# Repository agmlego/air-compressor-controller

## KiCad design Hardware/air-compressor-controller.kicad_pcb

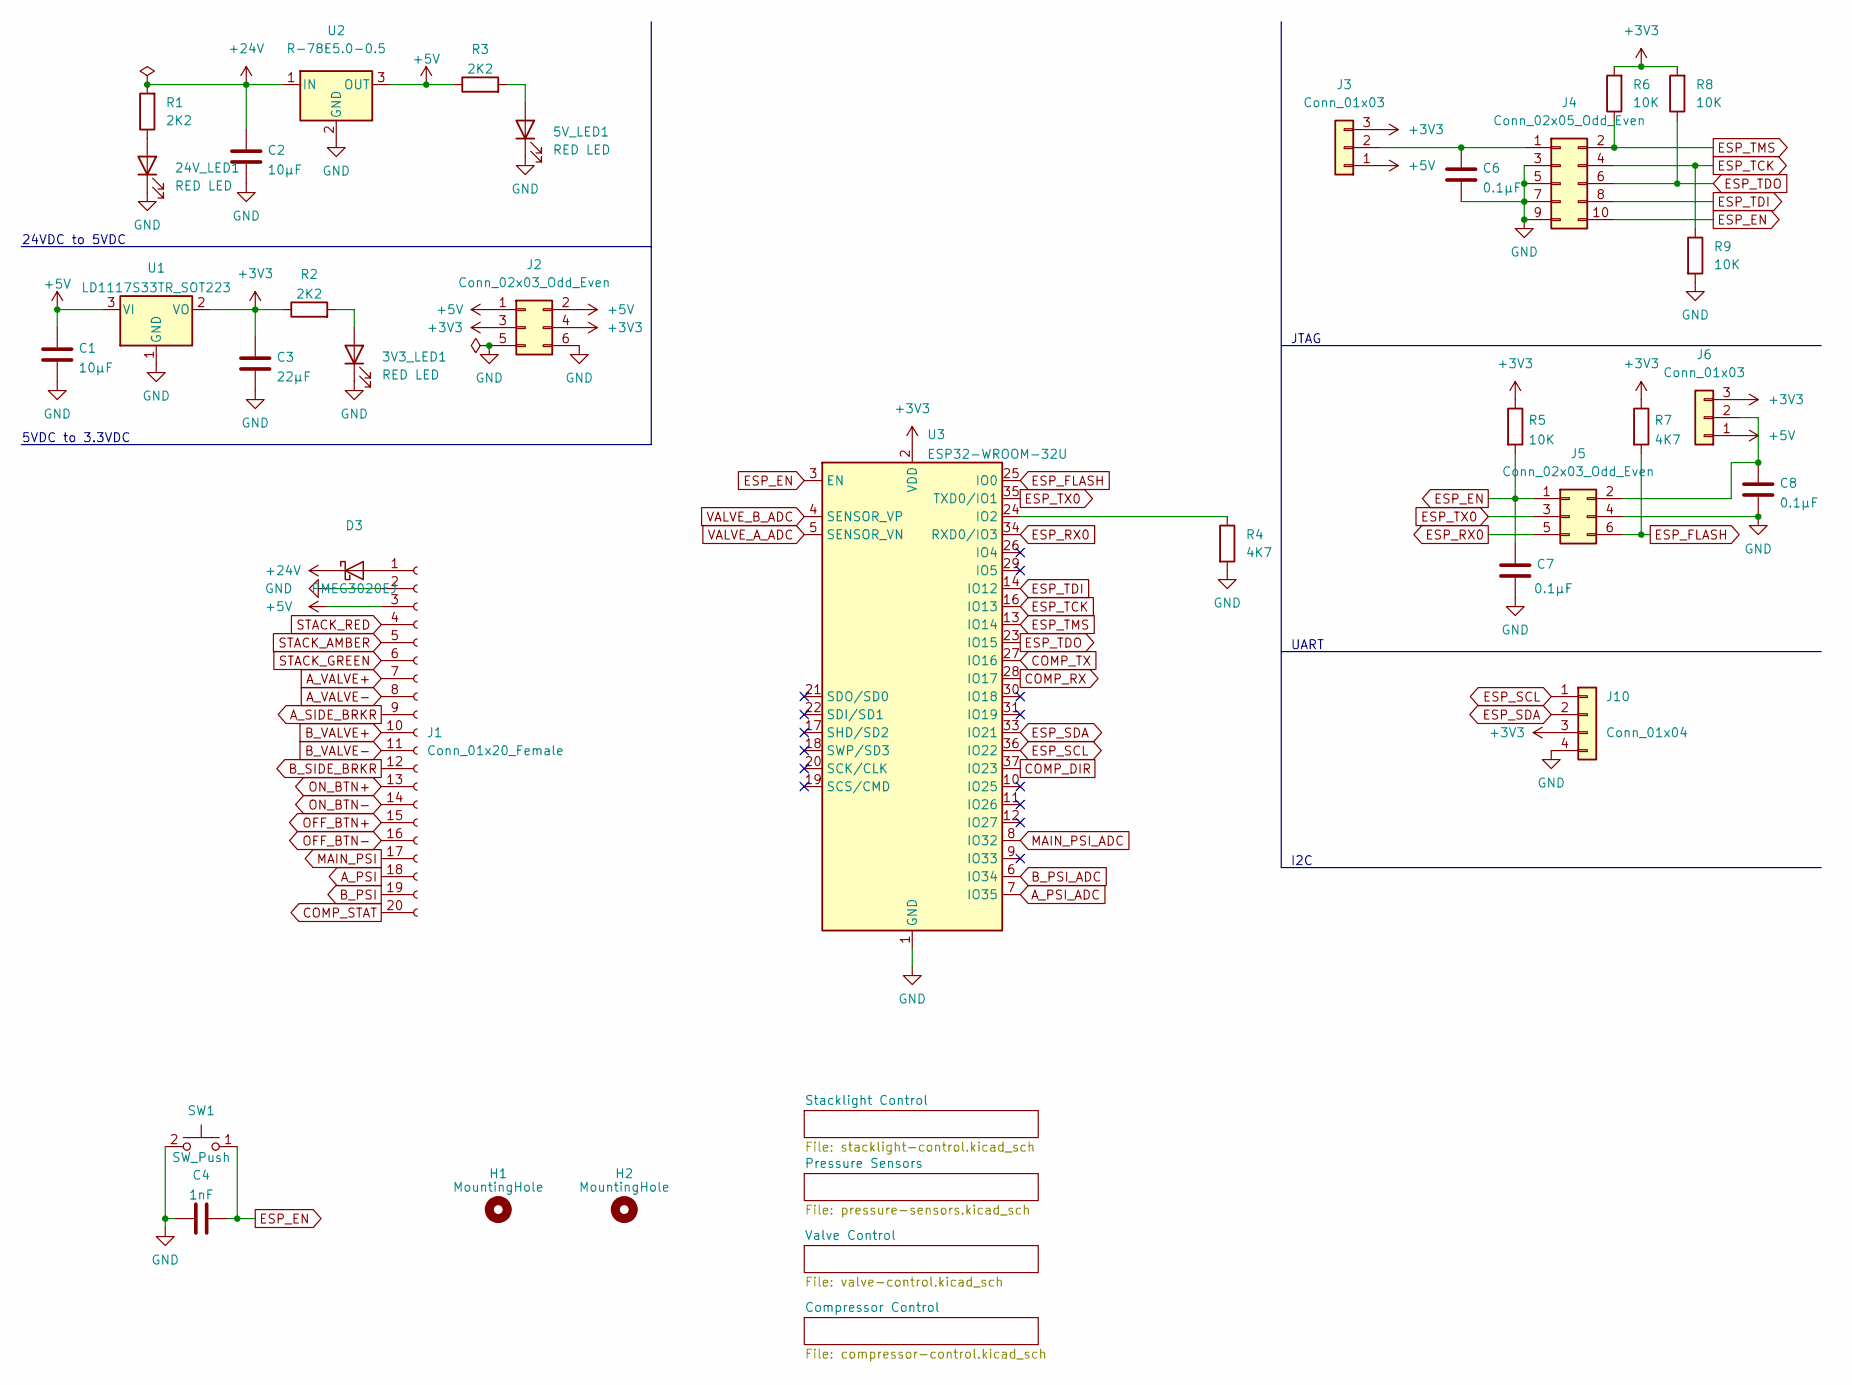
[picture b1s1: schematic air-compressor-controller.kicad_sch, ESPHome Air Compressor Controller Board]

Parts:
3V3_LED1, 5V_LED1, 24V_LED1: RED LED; LED_0603_1608Metric
C1, C2: 10µF; CP_Elec_4x4.5
C3: 22µF; CP_Elec_4x4.5
C4: 1nF; C_0603_1608Metric
C6, C7, C8: 0.1µF; C_0603_1608Metric
D3: PMEG3020EJ; D_SOD-323F
H1, H2: MountingHole; MountingHole_3.2mm_M3_Pad
J1: Conn_01x20_Female; Wago_734-180_1x20_P3.50mm_Horizontal
J2: Conn_02x03_Odd_Even; PinHeader_2x03_P2.54mm_Vertical_SMD
J3, J6: Conn_01x03; PinHeader_1x03_P2.54mm_Vertical_SMD_Pin1Left
J4: Conn_02x05_Odd_Even; Tag-Connect_TC2050-IDC-NL_2x05_P1.27mm_Vertical
J5: Conn_02x03_Odd_Even; Tag-Connect_TC2030-IDC-NL_2x03_P1.27mm_Vertical
J10: Conn_01x04; PinHeader_1x04_P2.54mm_Vertical_SMD_Pin1Left
R1, R2, R3: 2K2; R_0603_1608Metric
R4, R7: 4K7; R_0603_1608Metric
R5, R6, R8, R9: 10K; R_0603_1608Metric
SW1: SW_Push; SW_Tactile_SPST_Angled_PTS645Vx39-2LFS
U1: LD1117S33TR_SOT223; SOT-223-3_TabPin2
U2: R-78E5.0-0.5; Converter_DCDC_RECOM_R-78E-0.5_THT
U3: ESP32-WROOM-32U

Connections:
+3V3: C3.1, J2.3, J2.4, J3.3, J6.3, J10.3, R2.1, R5.1, R6.2, R7.1, R8.2, U1.2 (VO), U3.2 (VDD); also elsewhere on the board
+5V: C1.1, J1.3, J2.1, J2.2, J3.1, J6.1, R3.1, U1.3 (VI), U2.3 (OUT); also elsewhere on the board
+24V: C2.1, D3.1 (K), R1.2, U2.1 (IN); also elsewhere on the board
A_PSI: J1.18; also elsewhere on the board
A_PSI_ADC: U3.7 (IO35); also elsewhere on the board
A_SIDE_BRKR: J1.9; also elsewhere on the board
A_VALVE+: J1.7; also elsewhere on the board
A_VALVE-: J1.8; also elsewhere on the board
B_PSI: J1.19; also elsewhere on the board
B_PSI_ADC: U3.6 (IO34); also elsewhere on the board
B_SIDE_BRKR: J1.12; also elsewhere on the board
B_VALVE+: J1.10; also elsewhere on the board
B_VALVE-: J1.11; also elsewhere on the board
COMP_DIR: U3.37 (IO23); also elsewhere on the board
COMP_RX: U3.28 (IO17); also elsewhere on the board
COMP_STAT: J1.20; also elsewhere on the board
COMP_TX: U3.27 (IO16); also elsewhere on the board
ESP_EN: C4.2, C7.1, J4.10, J5.1, R5.2, SW1.1, U3.3 (EN); also elsewhere on the board
ESP_FLASH: J5.6, R7.2, U3.25 (IO0)
ESP_RX0: J5.5, U3.34 (RXD0/IO3)
ESP_SCL: J10.1, U3.36 (IO22); also elsewhere on the board
ESP_SDA: J10.2, U3.33 (IO21); also elsewhere on the board
ESP_TCK: J4.4, R9.1, U3.16 (IO13)
ESP_TDI: J4.8, U3.14 (IO12)
ESP_TDO: J4.6, R8.1, U3.23 (IO15)
ESP_TMS: J4.2, R6.1, U3.13 (IO14)
ESP_TX0: J5.3, U3.35 (TXD0/IO1)
GND: 3V3_LED1.1 (K), 5V_LED1.1 (K), 24V_LED1.1 (K), C1.2, C2.2, C3.2, C4.1, C6.2, C7.2, C8.2, J1.2, J2.5, J2.6, J4.3, J4.5, J4.7, J4.9, J5.4, J10.4, R4.2, R9.2, SW1.2, U1.1 (GND), U2.2 (GND), U3.1 (GND), U3.15 (GND), U3.38 (GND), U3.39 (GND); also elsewhere on the board
MAIN_PSI: J1.17; also elsewhere on the board
MAIN_PSI_ADC: U3.8 (IO32); also elsewhere on the board
unnamed: 3V3_LED1.2 (A), R2.2
unnamed: 5V_LED1.2 (A), R3.2
unnamed: 24V_LED1.2 (A), R1.1
unnamed: C6.1, J3.2, J4.1
unnamed: C8.1, J5.2, J6.2
unnamed: D3.2 (A), J1.1
unnamed: R4.1, U3.24 (IO2)
OFF_BTN+: J1.15; also elsewhere on the board
OFF_BTN-: J1.16; also elsewhere on the board
ON_BTN+: J1.13; also elsewhere on the board
ON_BTN-: J1.14; also elsewhere on the board
STACK_AMBER: J1.5; also elsewhere on the board
STACK_GREEN: J1.6; also elsewhere on the board
STACK_RED: J1.4; also elsewhere on the board
VALVE_A_ADC: U3.5 (SENSOR_VN); also elsewhere on the board
VALVE_B_ADC: U3.4 (SENSOR_VP); also elsewhere on the board

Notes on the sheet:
JTAG
UART
I2C
24VDC to 5VDC
5VDC to 3.3VDC

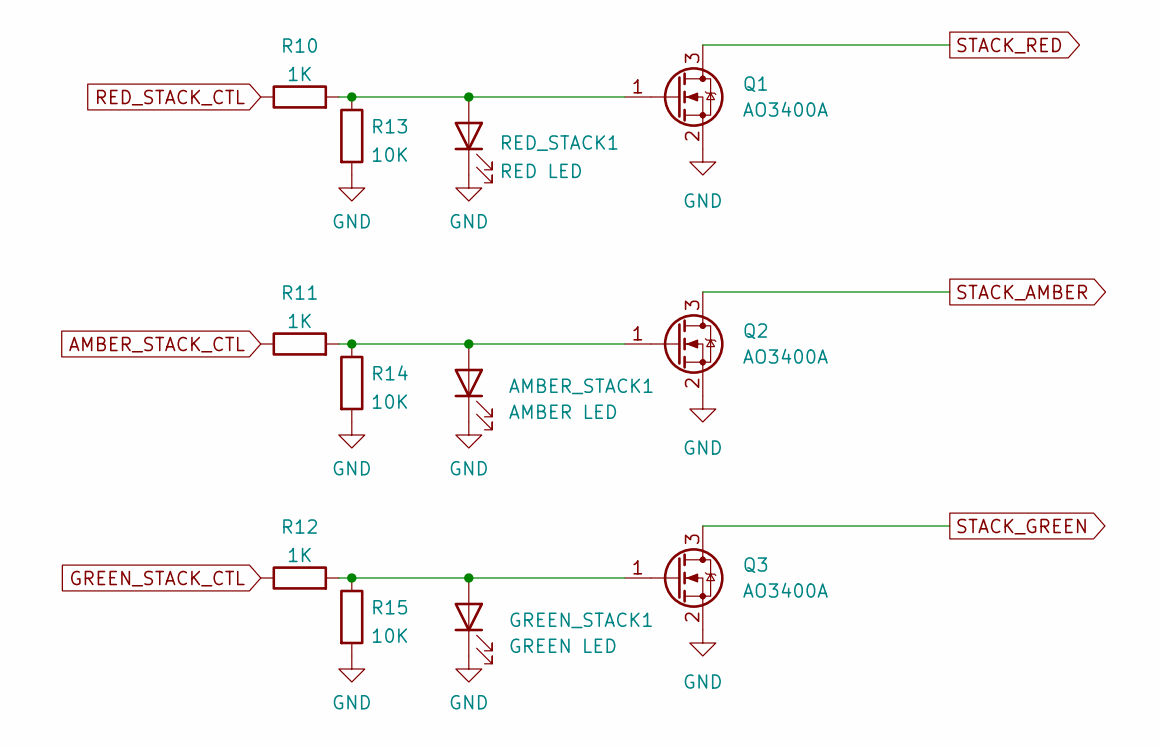
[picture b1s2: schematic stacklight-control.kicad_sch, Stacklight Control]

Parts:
AMBER_STACK1: AMBER LED; LED_0603_1608Metric
GREEN_STACK1: GREEN LED; LED_0603_1608Metric
Q1, Q2, Q3: AO3400A; SOT-23
R10, R11, R12: 1K; R_0603_1608Metric
R13, R14, R15: 10K; R_0603_1608Metric
RED_STACK1: RED LED; LED_0603_1608Metric

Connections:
AMBER_STACK_CTL: R11.1; also elsewhere on the board
GND: AMBER_STACK1.1 (K), GREEN_STACK1.1 (K), Q1.2 (S), Q2.2 (S), Q3.2 (S), R13.2, R14.2, R15.2, RED_STACK1.1 (K); also elsewhere on the board
GREEN_STACK_CTL: R12.1; also elsewhere on the board
unnamed: AMBER_STACK1.2 (A), Q2.1 (G), R11.2, R14.1
unnamed: GREEN_STACK1.2 (A), Q3.1 (G), R12.2, R15.1
unnamed: Q1.1 (G), R10.2, R13.1, RED_STACK1.2 (A)
RED_STACK_CTL: R10.1; also elsewhere on the board
STACK_AMBER: Q2.3 (D); also elsewhere on the board
STACK_GREEN: Q3.3 (D); also elsewhere on the board
STACK_RED: Q1.3 (D); also elsewhere on the board

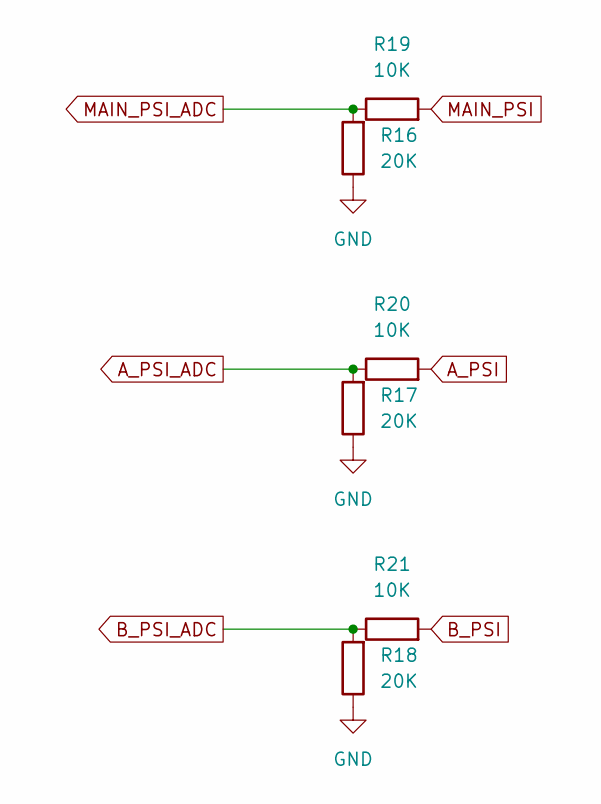
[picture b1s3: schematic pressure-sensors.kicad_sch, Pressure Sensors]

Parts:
R16, R17, R18: 20K; R_0603_1608Metric
R19, R20, R21: 10K; R_0603_1608Metric

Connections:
A_PSI: R20.2; also elsewhere on the board
A_PSI_ADC: R17.2, R20.1; also elsewhere on the board
B_PSI: R21.2; also elsewhere on the board
B_PSI_ADC: R18.2, R21.1; also elsewhere on the board
GND: R16.1, R17.1, R18.1; also elsewhere on the board
MAIN_PSI: R19.2; also elsewhere on the board
MAIN_PSI_ADC: R16.2, R19.1; also elsewhere on the board

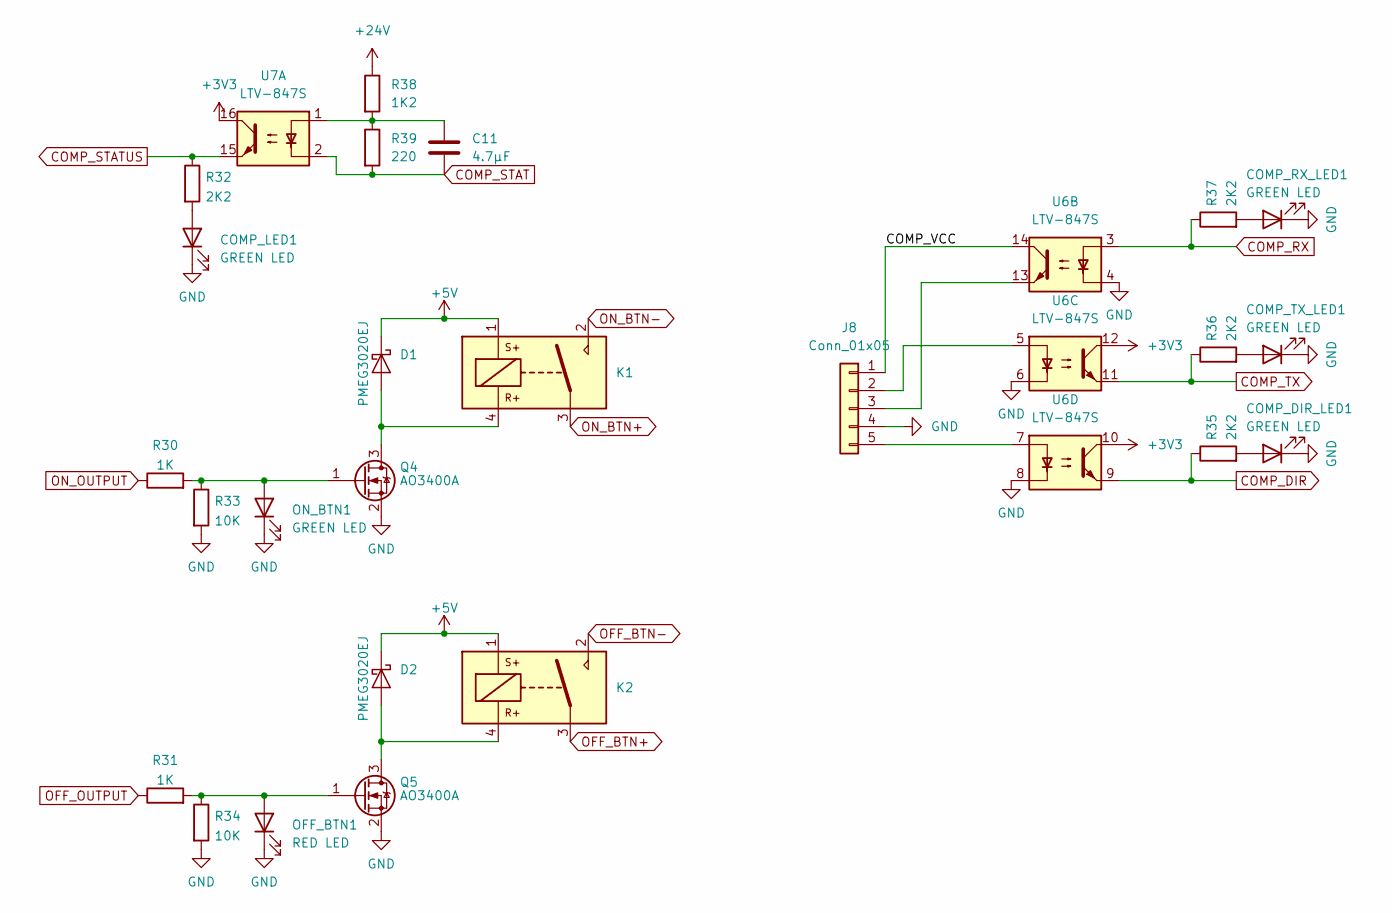
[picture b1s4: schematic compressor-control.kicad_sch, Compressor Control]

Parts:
C11: 4.7μF; C_0603_1608Metric
COMP_DIR_LED1: GREEN LED; LED_0603_1608Metric
COMP_LED1: GREEN LED; LED_0603_1608Metric
COMP_RX_LED1: GREEN LED; LED_0603_1608Metric
COMP_TX_LED1: GREEN LED; LED_0603_1608Metric
D1, D2: PMEG3020EJ; D_SOD-323F
J8: Conn_01x05; Molex_KK-254_AE-6410-05A_1x05_P2.54mm_Vertical
K1, K2: sonoff_relay; sonoff relay
OFF_BTN1: RED LED; LED_0603_1608Metric
ON_BTN1: GREEN LED; LED_0603_1608Metric
Q4, Q5: AO3400A; SOT-23
R30, R31: 1K; R_0603_1608Metric
R32, R35, R36, R37: 2K2; R_0603_1608Metric
R33, R34: 10K; R_0603_1608Metric
R38: 1K2; R_0603_1608Metric
R39: 220; R_0603_1608Metric
U6, U7: LTV-847S; SMDIP-16_W9.53mm

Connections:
+3V3: U6.10, U6.12, U7.16; also elsewhere on the board
+5V: D1.1 (K), D2.1 (K), K1.1, K2.1; also elsewhere on the board
+24V: R38.1; also elsewhere on the board
/Compressor Control/COMP_VCC: J8.1, U6.14
COMP_DIR: R35.1, U6.9; also elsewhere on the board
COMP_RX: R37.1, U6.3; also elsewhere on the board
COMP_STAT: C11.1, R39.2, U7.2; also elsewhere on the board
COMP_STATUS: R32.1, U7.15; also elsewhere on the board
COMP_TX: R36.1, U6.11; also elsewhere on the board
GND: COMP_DIR_LED1.1 (K), COMP_LED1.1 (K), COMP_RX_LED1.1 (K), COMP_TX_LED1.1 (K), J8.4, OFF_BTN1.1 (K), ON_BTN1.1 (K), Q4.2 (S), Q5.2 (S), R33.2, R34.2, U6.4, U6.6, U6.8; also elsewhere on the board
unnamed: C11.2, R38.2, R39.1, U7.1
unnamed: COMP_DIR_LED1.2 (A), R35.2
unnamed: COMP_LED1.2 (A), R32.2
unnamed: COMP_RX_LED1.2 (A), R37.2
unnamed: COMP_TX_LED1.2 (A), R36.2
unnamed: D1.2 (A), K1.4, Q4.3 (D)
unnamed: D2.2 (A), K2.4, Q5.3 (D)
unnamed: J8.2, U6.5
unnamed: J8.3, U6.13
unnamed: J8.5, U6.7
unnamed: OFF_BTN1.2 (A), Q5.1 (G), R31.2, R34.1
unnamed: ON_BTN1.2 (A), Q4.1 (G), R30.2, R33.1
OFF_BTN+: K2.3; also elsewhere on the board
OFF_BTN-: K2.2; also elsewhere on the board
OFF_OUTPUT: R31.1; also elsewhere on the board
ON_BTN+: K1.3; also elsewhere on the board
ON_BTN-: K1.2; also elsewhere on the board
ON_OUTPUT: R30.1; also elsewhere on the board

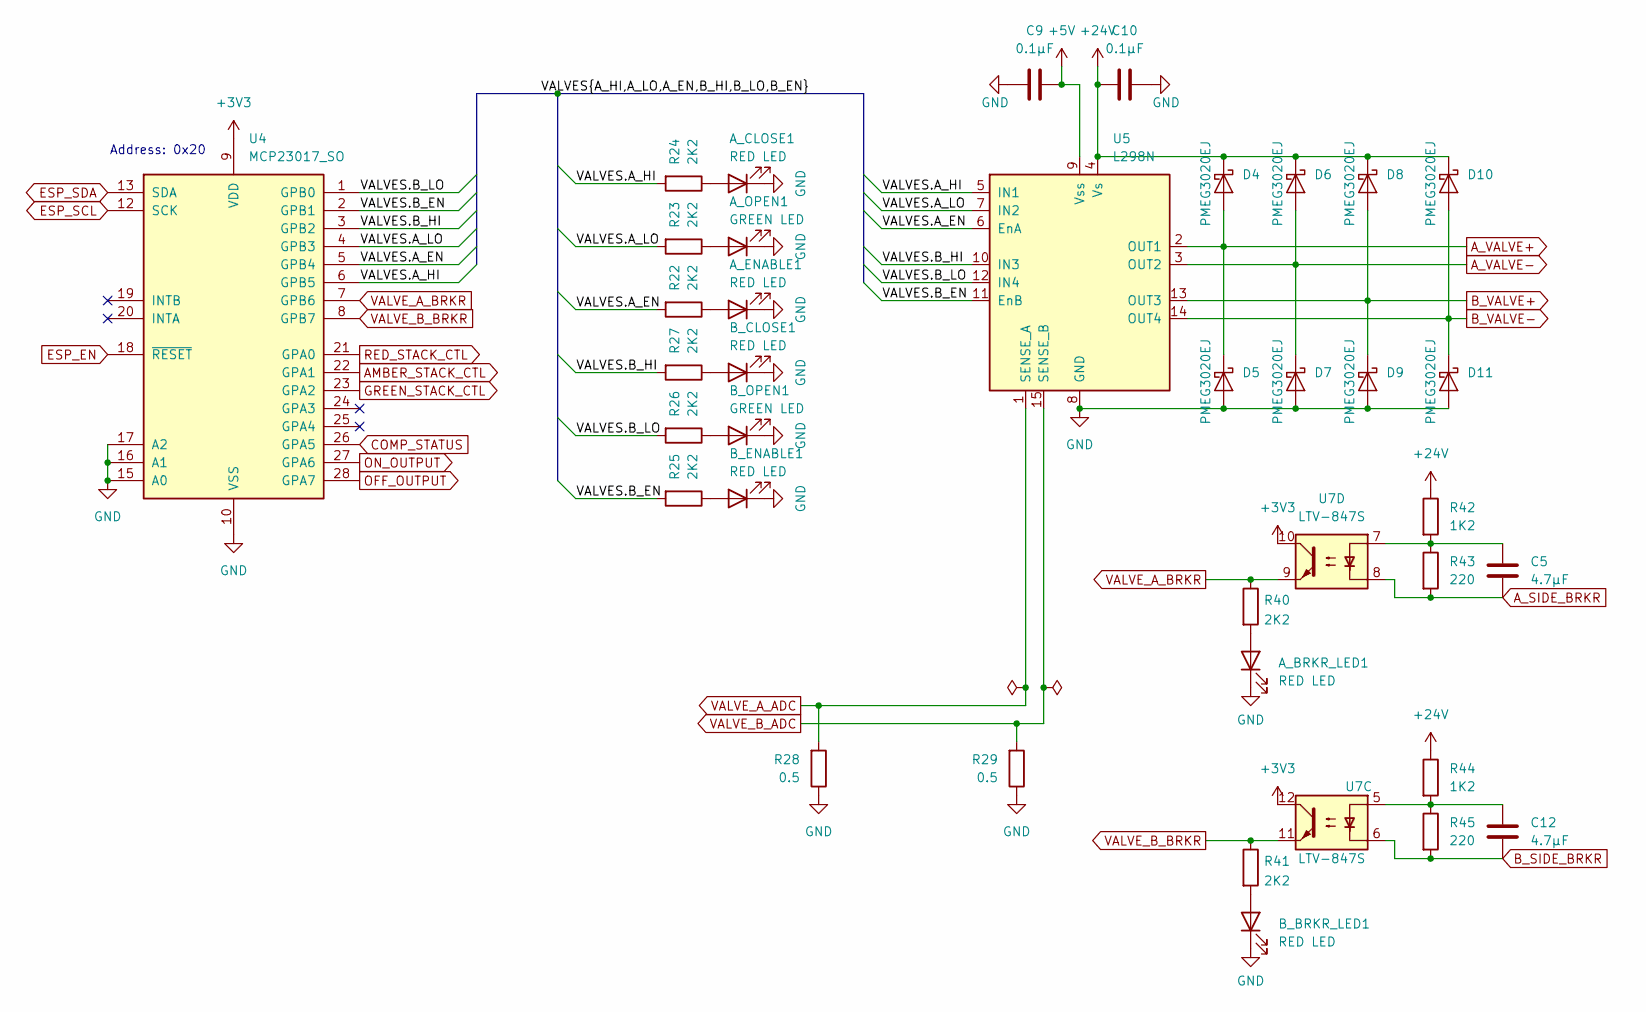
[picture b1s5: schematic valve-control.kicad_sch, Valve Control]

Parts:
A_BRKR_LED1: RED LED; LED_0603_1608Metric
A_CLOSE1: RED LED; LED_0603_1608Metric
A_ENABLE1: RED LED; LED_0603_1608Metric
A_OPEN1: GREEN LED; LED_0603_1608Metric
B_BRKR_LED1: RED LED; LED_0603_1608Metric
B_CLOSE1: RED LED; LED_0603_1608Metric
B_ENABLE1: RED LED; LED_0603_1608Metric
B_OPEN1: GREEN LED; LED_0603_1608Metric
C5, C12: 4.7μF; C_0603_1608Metric
C9, C10: 0.1µF; C_0603_1608Metric
D4, D5, D6, D7, D8, D9, D10, D11: PMEG3020EJ; D_SOD-323F
R22, R23, R24, R25, R26, R27, R40, R41: 2K2; R_0603_1608Metric
R28, R29: 0.5; R_1206_3216Metric
R42, R44: 1K2; R_0603_1608Metric
R43, R45: 220; R_0603_1608Metric
U4: MCP23017_SO; SOIC-28W_7.5x17.9mm_P1.27mm
U5: L298N; TO-220-15_P2.54x2.54mm_StaggerOdd_Lead4.58mm_Vertical
U7: LTV-847S; SMDIP-16_W9.53mm

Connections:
+3V3: U4.9 (VDD), U7.10, U7.12; also elsewhere on the board
+5V: C9.2, U5.9 (Vss); also elsewhere on the board
+24V: C10.1, D4.1 (K), D6.1 (K), D8.1 (K), D10.1 (K), R42.1, R44.1, U5.4 (Vs); also elsewhere on the board
/Valve Control/VALVES.A_EN: R22.2, U4.5 (GPB4), U5.6 (EnA)
/Valve Control/VALVES.A_HI: R24.2, U4.6 (GPB5), U5.5 (IN1)
/Valve Control/VALVES.A_LO: R23.2, U4.4 (GPB3), U5.7 (IN2)
/Valve Control/VALVES.B_EN: R25.2, U4.2 (GPB1), U5.11 (EnB)
/Valve Control/VALVES.B_HI: R27.2, U4.3 (GPB2), U5.10 (IN3)
/Valve Control/VALVES.B_LO: R26.2, U4.1 (GPB0), U5.12 (IN4)
AMBER_STACK_CTL: U4.22 (GPA1); also elsewhere on the board
A_SIDE_BRKR: C5.1, R43.2, U7.8; also elsewhere on the board
A_VALVE+: D4.2 (A), D5.1 (K), U5.2 (OUT1); also elsewhere on the board
A_VALVE-: D6.2 (A), D7.1 (K), U5.3 (OUT2); also elsewhere on the board
B_SIDE_BRKR: C12.1, R45.2, U7.6; also elsewhere on the board
B_VALVE+: D8.2 (A), D9.1 (K), U5.13 (OUT3); also elsewhere on the board
B_VALVE-: D10.2 (A), D11.1 (K), U5.14 (OUT4); also elsewhere on the board
COMP_STATUS: U4.26 (GPA5); also elsewhere on the board
ESP_EN: U4.18 (~RESET); also elsewhere on the board
ESP_SCL: U4.12 (SCK); also elsewhere on the board
ESP_SDA: U4.13 (SDA); also elsewhere on the board
GND: A_BRKR_LED1.1 (K), A_CLOSE1.1 (K), A_ENABLE1.1 (K), A_OPEN1.1 (K), B_BRKR_LED1.1 (K), B_CLOSE1.1 (K), B_ENABLE1.1 (K), B_OPEN1.1 (K), C9.1, C10.2, D5.2 (A), D7.2 (A), D9.2 (A), D11.2 (A), R28.1, R29.1, U4.10 (VSS), U4.15 (A0), U4.16 (A1), U4.17 (A2), U5.8 (GND); also elsewhere on the board
GREEN_STACK_CTL: U4.23 (GPA2); also elsewhere on the board
unnamed: A_BRKR_LED1.2 (A), R40.2
unnamed: A_CLOSE1.2 (A), R24.1
unnamed: A_ENABLE1.2 (A), R22.1
unnamed: A_OPEN1.2 (A), R23.1
unnamed: B_BRKR_LED1.2 (A), R41.2
unnamed: B_CLOSE1.2 (A), R27.1
unnamed: B_ENABLE1.2 (A), R25.1
unnamed: B_OPEN1.2 (A), R26.1
unnamed: C5.2, R42.2, R43.1, U7.7
unnamed: C12.2, R44.2, R45.1, U7.5
OFF_OUTPUT: U4.28 (GPA7); also elsewhere on the board
ON_OUTPUT: U4.27 (GPA6); also elsewhere on the board
RED_STACK_CTL: U4.21 (GPA0); also elsewhere on the board
VALVE_A_ADC: R28.2, U5.1 (SENSE_A); also elsewhere on the board
VALVE_A_BRKR: R40.1, U4.7 (GPB6), U7.9
VALVE_B_ADC: R29.2, U5.15 (SENSE_B); also elsewhere on the board
VALVE_B_BRKR: R41.1, U4.8 (GPB7), U7.11

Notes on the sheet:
Address: 0x20

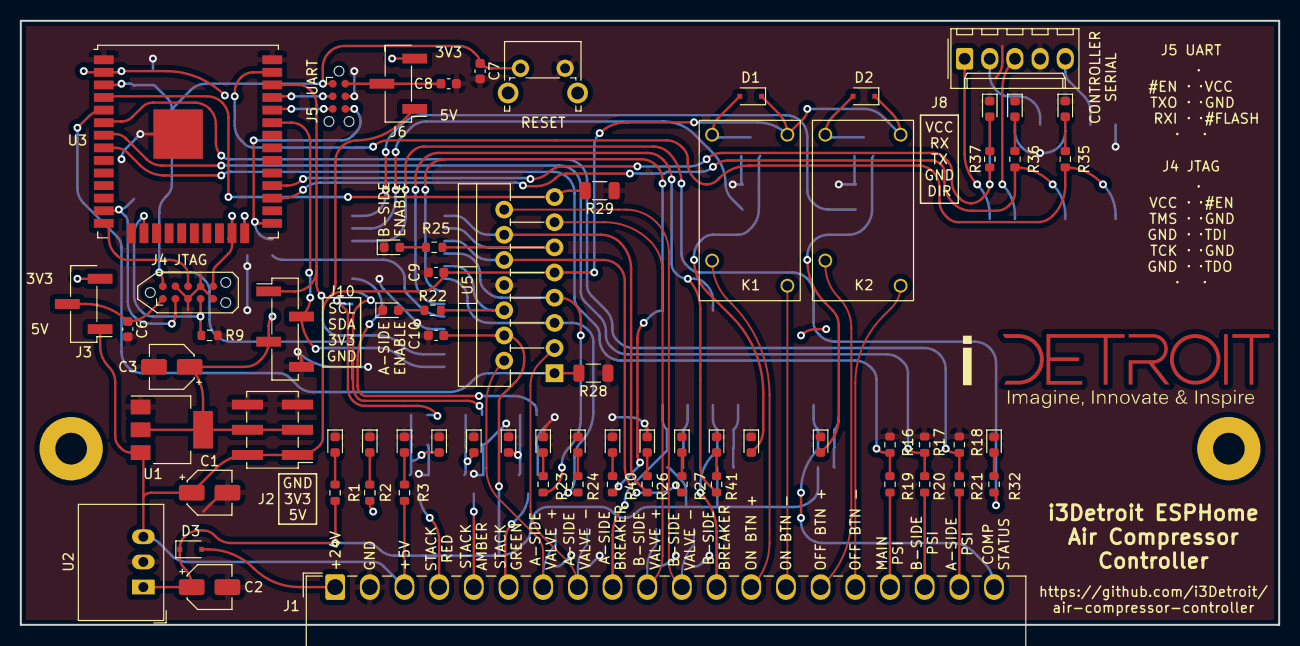
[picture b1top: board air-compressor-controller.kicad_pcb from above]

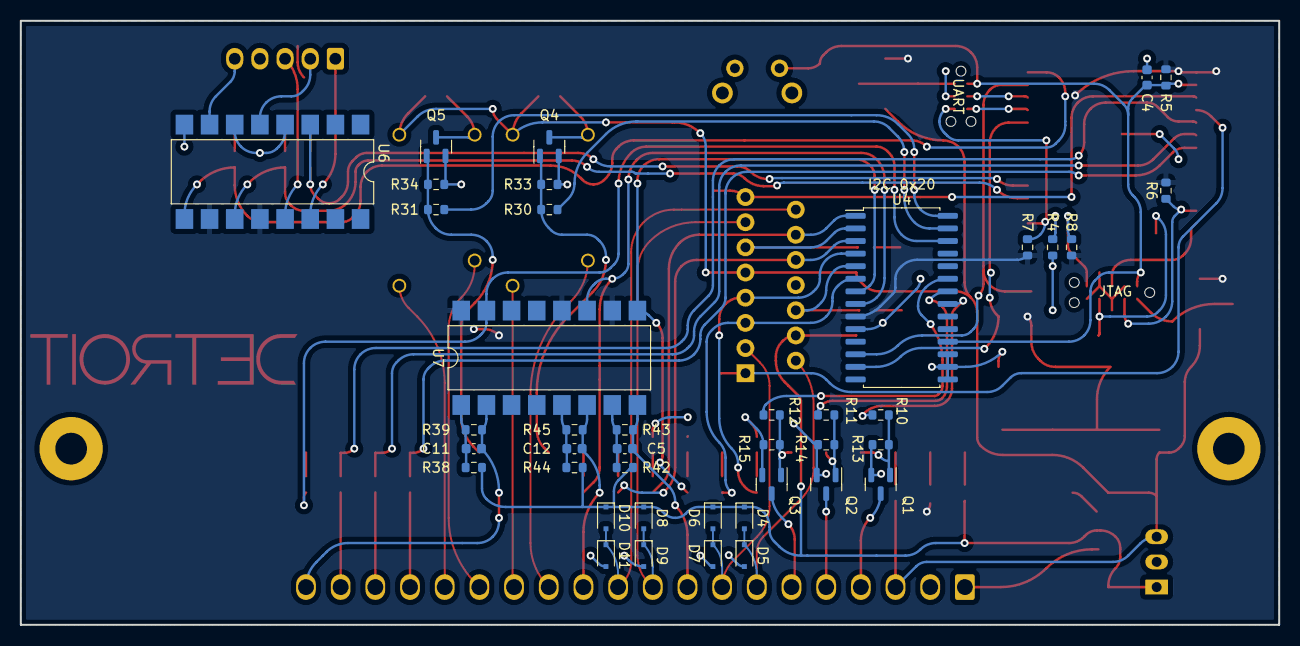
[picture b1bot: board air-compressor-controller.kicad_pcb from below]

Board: 2 copper layers, 127.0 x 61.0 mm, 113 parts (41 on the bottom side), 86 nets.

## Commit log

2022-10-17 Initial schematic
2022-10-19 Move to organization structure
2022-10-19 Added I2C block
2022-10-19 Corrected relay footprints
2022-10-19 Removed Zener diodes on ADC channels
2022-10-19 Update gitignore for autosaves
2022-10-19 Beginning of PCB layout
2022-11-07 Added breakout to terminal blocks
2022-11-07 Changed connectors to a common header, much routing done.
2022-11-17 Finalised routing, silkscreen yet to do
2022-11-17 Silk and routing complete.
2022-11-18 Added flyback diodes to L298N outputs
2023-01-03 Actually routed stacklight control pins...
2023-01-04 Added interactive BOM
